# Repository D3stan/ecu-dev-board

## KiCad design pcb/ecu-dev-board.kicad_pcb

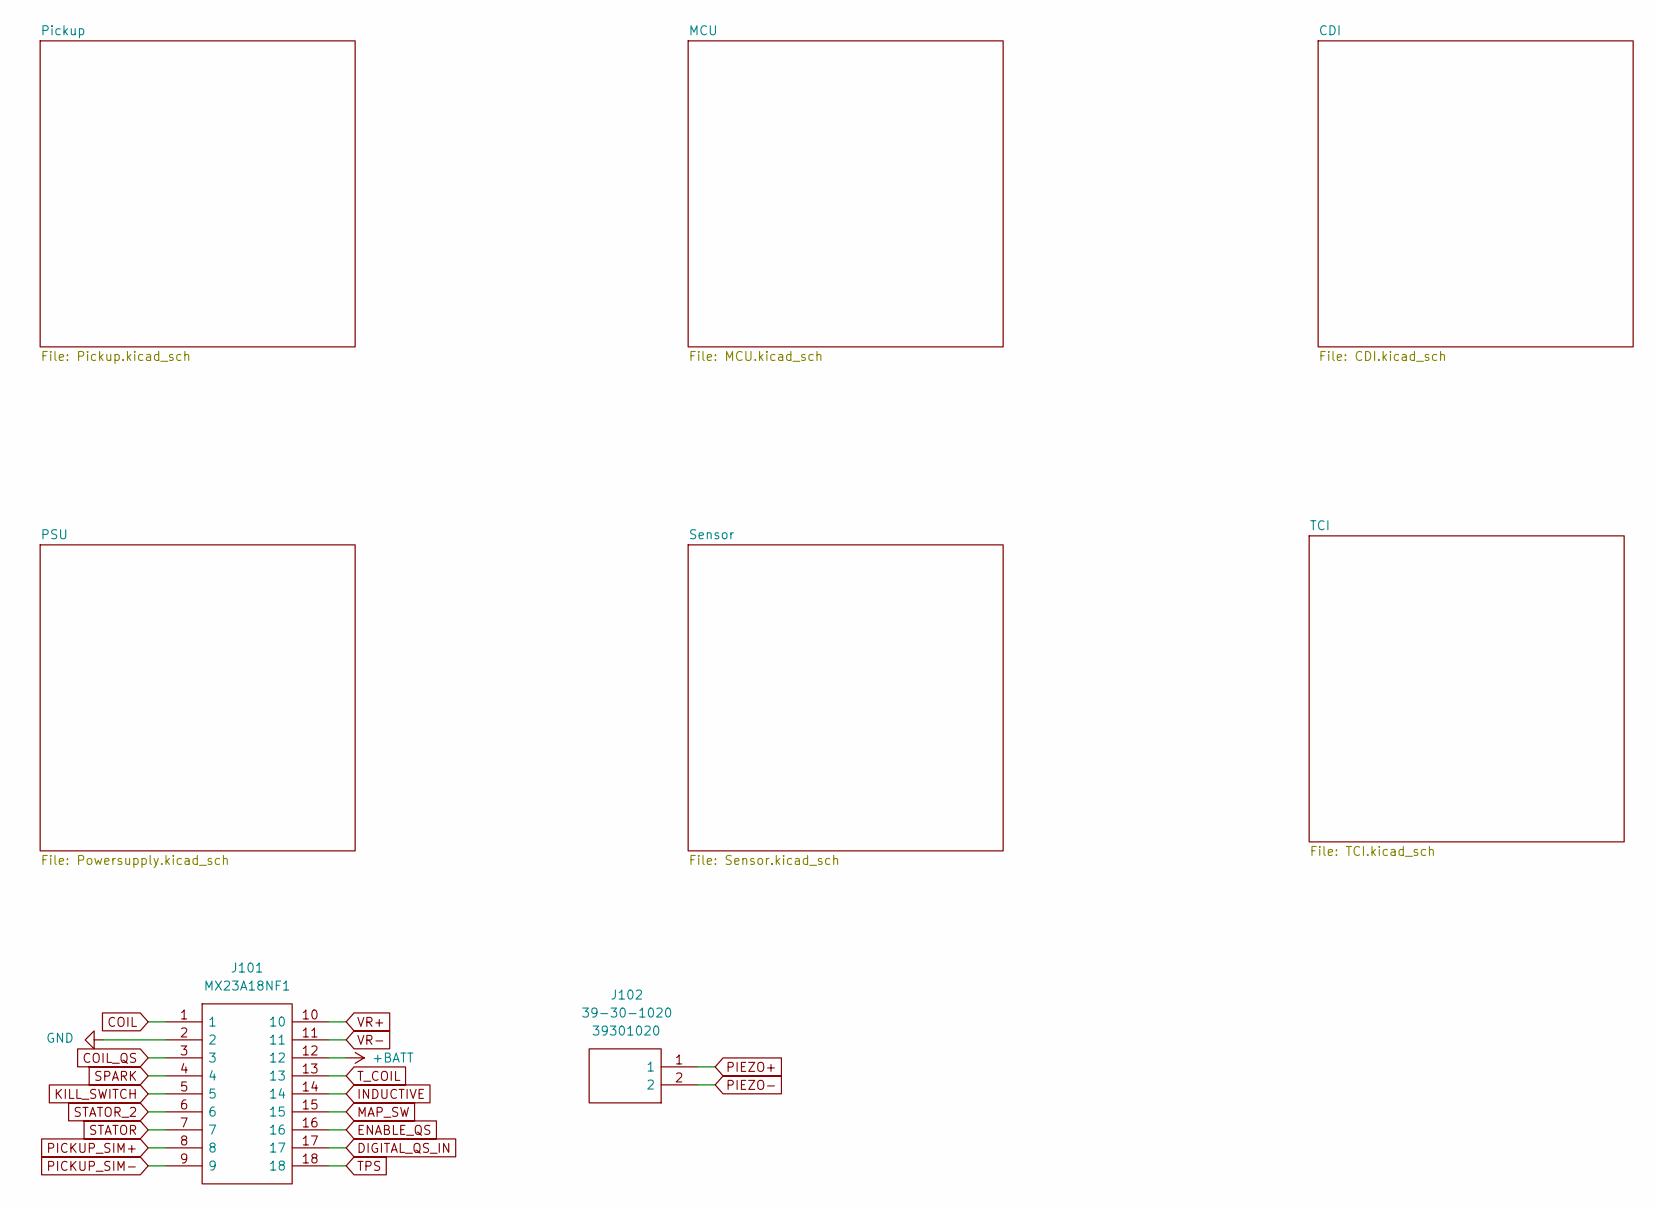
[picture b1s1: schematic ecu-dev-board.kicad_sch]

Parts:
J101: MX23A18NF1; Manufacturer_Part_Number MX23A18NF1; Mouser Part Number 656-MX23A18NF1
J102: 39-30-1020; Molex_Mini-Fit_Jr_5569-02A2_2x01_P4.20mm_Horizontal; Manufacturer_Part_Number 39301020; Mouser Part Number 538-39-30-1020

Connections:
+BATT: J101.12; also elsewhere on the board
COIL: J101.1; also elsewhere on the board
COIL_QS: J101.3; also elsewhere on the board
DIGITAL_QS_IN: J101.17; also elsewhere on the board
ENABLE_QS: J101.16; also elsewhere on the board
INDUCTIVE: J101.14; also elsewhere on the board
KILL_SWITCH: J101.5; also elsewhere on the board
MAP_SW: J101.15; also elsewhere on the board
PICKUP_SIM+: J101.8; also elsewhere on the board
PICKUP_SIM-: J101.9; also elsewhere on the board
PIEZO+: J102.1; also elsewhere on the board
PIEZO-: J102.2; also elsewhere on the board
SPARK: J101.4; also elsewhere on the board
STATOR: J101.7; also elsewhere on the board
STATOR_2: J101.6; also elsewhere on the board
TPS: J101.18; also elsewhere on the board
T_COIL: J101.13; also elsewhere on the board
VR+: J101.10; also elsewhere on the board
VR-: J101.11; also elsewhere on the board

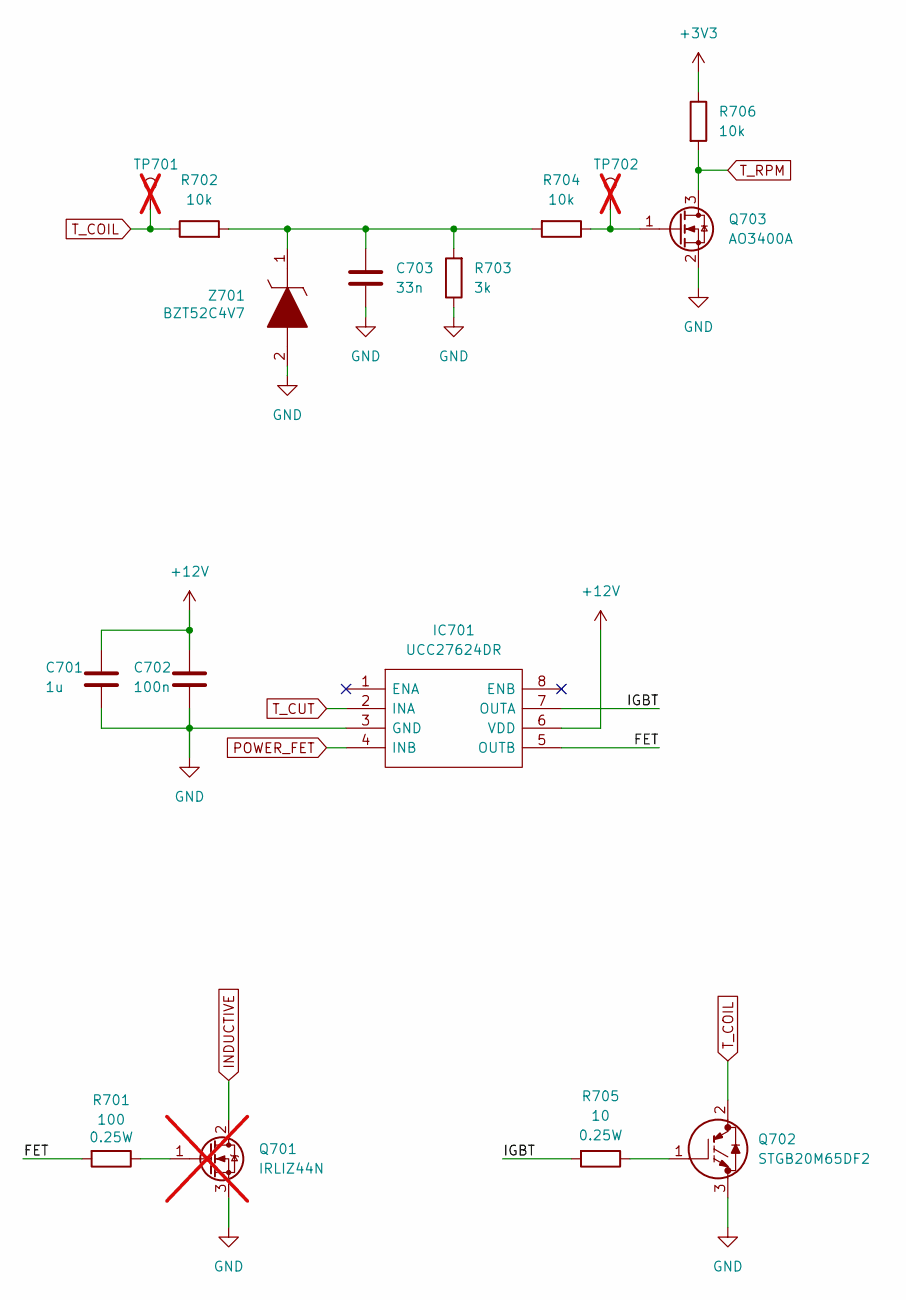
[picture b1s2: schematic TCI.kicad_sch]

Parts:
C701: 1u; C_0805_2012Metric
C702: 100n; C_0805_2012Metric
C703: 33n; C_0805_2012Metric
IC701: UCC27624DR; SOIC127P600X175-8N; Manufacturer_Part_Number UCC27624QDRQ1; Mouser Part Number 595-UCC27624QDRQ1
Q701: IRLIZ44N; TO-220F-3_Vertical; not fitted
Q702: STGB20M65DF2; TO-263-2; Manufacturer_Part_Number STGB20M65DF2; Mouser Part Number 511-STGB20M65DF2
Q703: AO3400A; SOT-23
R701: 100; R_0805_2012Metric
R702, R704, R706: 10k; R_0805_2012Metric
R703: 3k; R_0805_2012Metric
R705: 10; R_0805_2012Metric
TP701, TP702: TestPoint; PinHeader_1x01_P2.54mm_Vertical; not fitted
Z701: BZT52C4V7; D_SOD-123; Manufacturer_Part_Number BZT52B5V1-E3-08; Mouser Part Number 78-BZT52B5V1-E3-08

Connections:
+3V3: R706.1; also elsewhere on the board
+12V: C701.1, C702.1, IC701.6 (VDD); also elsewhere on the board
/TCI/FET: IC701.5 (OUTB), R701.2
/TCI/IGBT: IC701.7 (OUTA), R705.2
INDUCTIVE: Q701.2 (D); also elsewhere on the board
unnamed: C703.1, R702.2, R703.2, R704.2, Z701.1
unnamed: Q701.1 (G), R701.1
unnamed: Q702.1, R705.1
unnamed: Q703.1 (G), R704.1, TP702.1
POWER_FET: IC701.4 (INB); also elsewhere on the board
T_COIL: Q702.2, R702.1, TP701.1; also elsewhere on the board
T_CUT: IC701.2 (INA); also elsewhere on the board
T_RPM: Q703.3 (D), R706.2; also elsewhere on the board

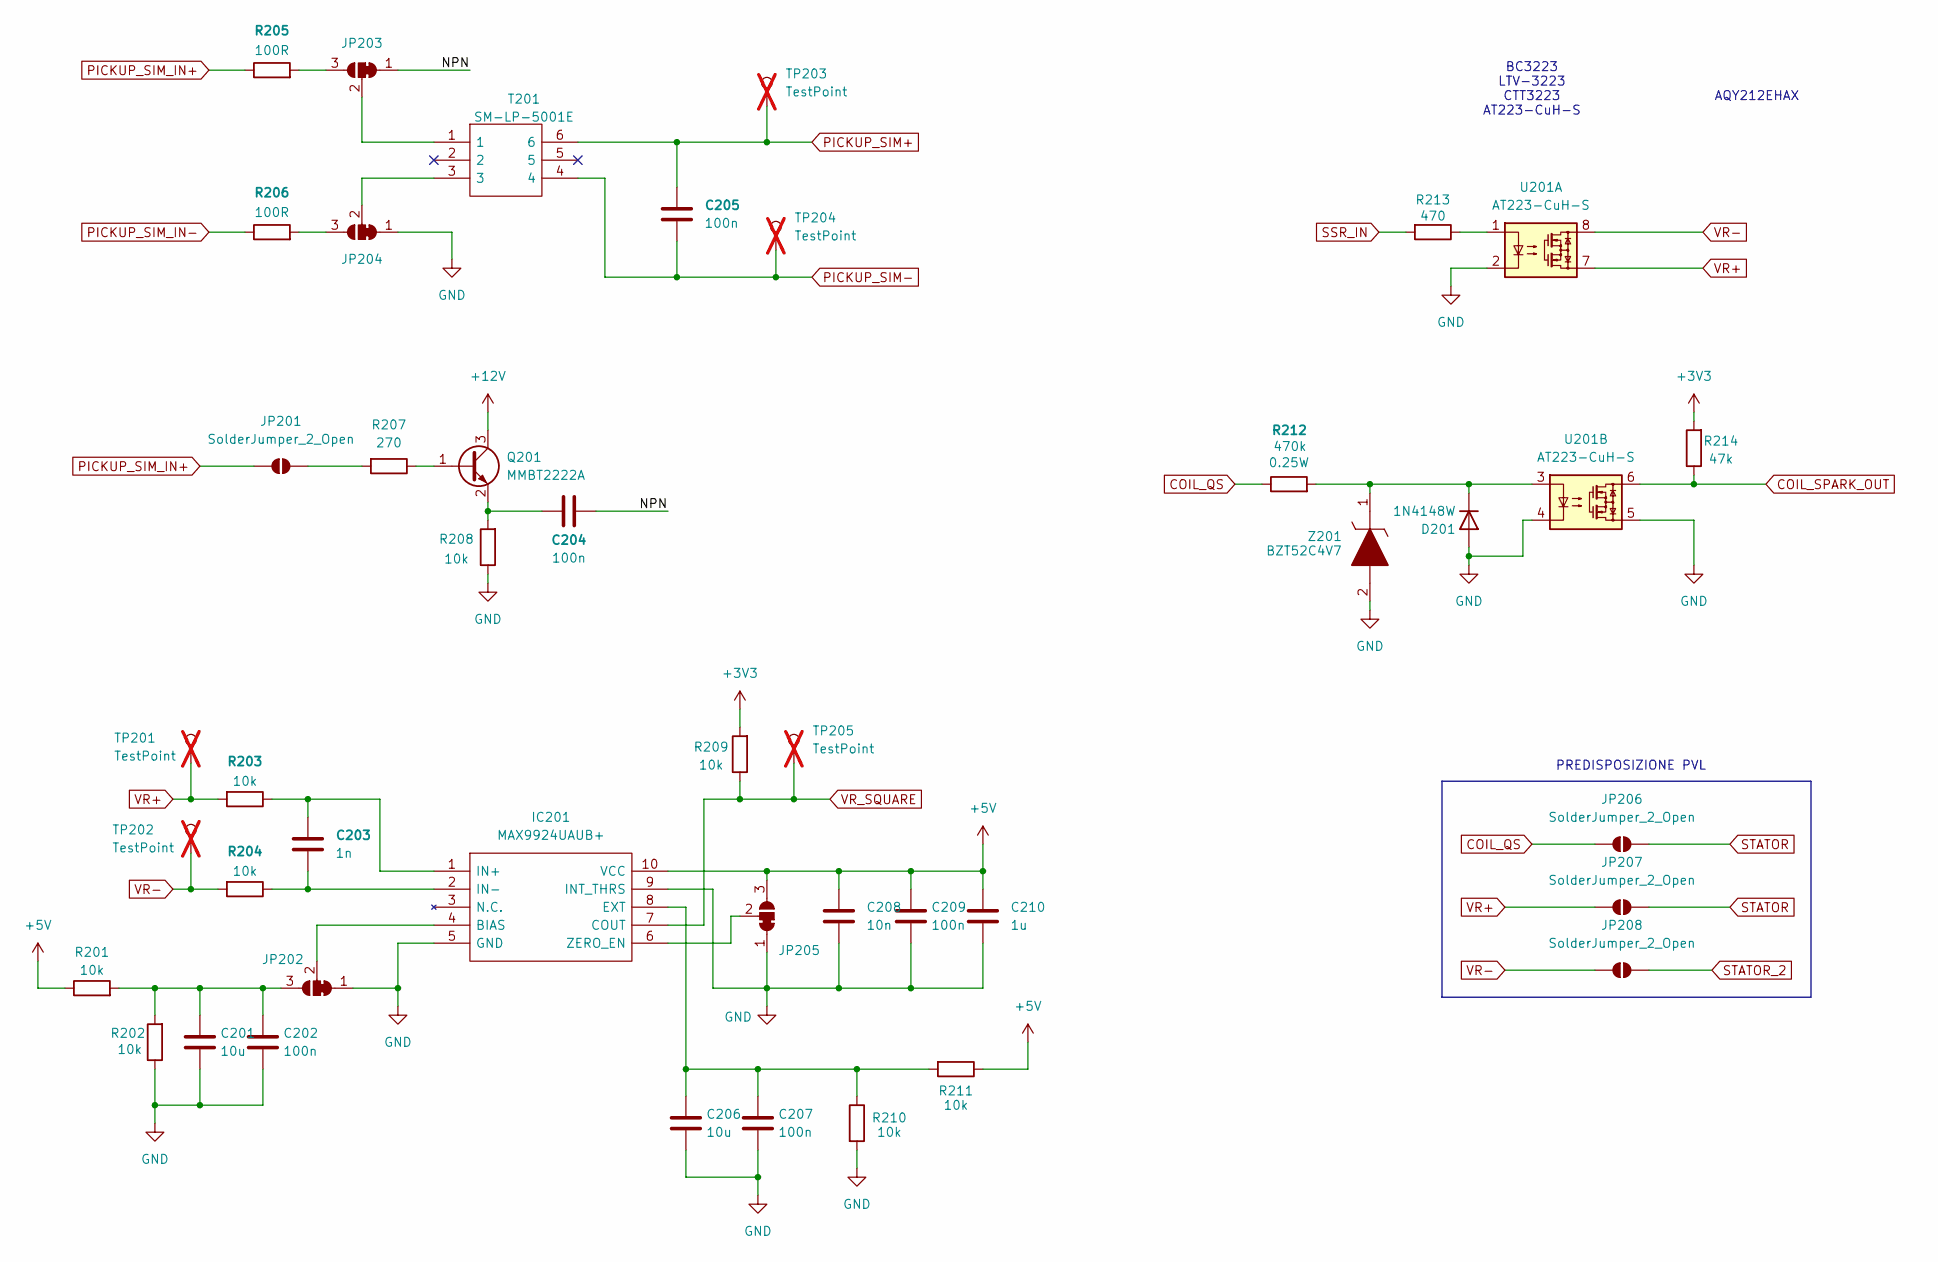
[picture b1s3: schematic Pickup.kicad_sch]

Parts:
C201, C206: 10u; C_0805_2012Metric
C202, C204, C205, C207, C209: 100n; C_0805_2012Metric
C203: 1n; C_0805_2012Metric
C208: 10n; C_0805_2012Metric
C210: 1u; C_0805_2012Metric
D201: 1N4148W; D_SOD-123
IC201: MAX9924UAUB+; SOP50P490X110-10N; Manufacturer_Part_Number MAX9924UAUB+; Mouser Part Number 700-MAX9924UAUB
JP201, JP206, JP207, JP208: SolderJumper_2_Open; SolderJumper-2_P1.3mm_Open_RoundedPad1.0x1.5mm
JP202, JP203, JP204, JP205: SolderJumper_3_Bridged12; SolderJumper-3_P1.3mm_Bridged2Bar12_RoundedPad1.0x1.5mm
Q201: MMBT2222A; SOT-23
R201, R202, R203, R204, R208, R209, R210, R211: 10k; R_0805_2012Metric
R205, R206: 100R; R_0805_2012Metric
R207: 270; R_0603_1608Metric
R212: 470k; R_0805_2012Metric
R213: 470; R_0805_2012Metric
R214: 47k; R_0805_2012Metric
T201: SM-LP-5001E; SMLP5001E; Manufacturer_Part_Number SM-LP-5001E; Mouser Part Number 652-SM-LP-5001E
TP201, TP202, TP203, TP204, TP205: TestPoint; PinHeader_1x01_P2.54mm_Vertical; not fitted
U201: AT223-CuH-S; SOP-8_6.605x9.655mm_P2.54mm
Z201: BZT52C4V7; D_SOD-123; Manufacturer_Part_Number BZT52B5V1-E3-08; Mouser Part Number 78-BZT52B5V1-E3-08

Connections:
+3V3: R209.2, R214.2; also elsewhere on the board
+5V: C208.1, C209.1, C210.1, IC201.10 (VCC), JP205.3 (B), R201.1, R211.1; also elsewhere on the board
+12V: Q201.3 (C); also elsewhere on the board
/Pickup/NPN: C204.1, JP203.1 (A)
COIL_QS: JP206.2 (B), R212.1; also elsewhere on the board
COIL_SPARK_OUT: R214.1, U201.6; also elsewhere on the board
unnamed: D201.1 (K), R212.2, U201.3, Z201.1
unnamed: IC201.4 (BIAS), JP202.2 (C)
unnamed: C206.1, C207.1, IC201.8 (EXT), R210.1, R211.2
unnamed: C203.1, IC201.1 (IN+), R203.1
unnamed: C203.2, IC201.2 (IN-), R204.1
unnamed: IC201.6 (ZERO_EN), JP205.2 (C)
unnamed: JP201.1 (A), R207.2
unnamed: C201.1, C202.1, JP202.3 (B), R201.2, R202.2
unnamed: JP203.3 (B), R205.2
unnamed: JP203.2 (C), T201.1
unnamed: JP204.3 (B), R206.2
unnamed: JP204.2 (C), T201.3
unnamed: Q201.1 (B), R207.1
unnamed: C204.2, Q201.2 (E), R208.2
unnamed: R213.1, U201.1
PICKUP_SIM+: C205.1, T201.6, TP203.1; also elsewhere on the board
PICKUP_SIM-: C205.2, T201.4, TP204.1; also elsewhere on the board
PICKUP_SIM_IN+: JP201.2 (B), R205.1; also elsewhere on the board
PICKUP_SIM_IN-: R206.1; also elsewhere on the board
SSR_IN: R213.2; also elsewhere on the board
STATOR: JP206.1 (A), JP207.1 (A); also elsewhere on the board
STATOR_2: JP208.1 (A); also elsewhere on the board
VR+: JP207.2 (B), R203.2, TP201.1, U201.7; also elsewhere on the board
VR-: JP208.2 (B), R204.2, TP202.1, U201.8; also elsewhere on the board
VR_SQUARE: IC201.7 (COUT), R209.1, TP205.1; also elsewhere on the board

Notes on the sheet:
BC3223 LTV-3223 CTT3223 AT223-CuH-S
PREDISPOSIZIONE PVL
AQY212EHAX

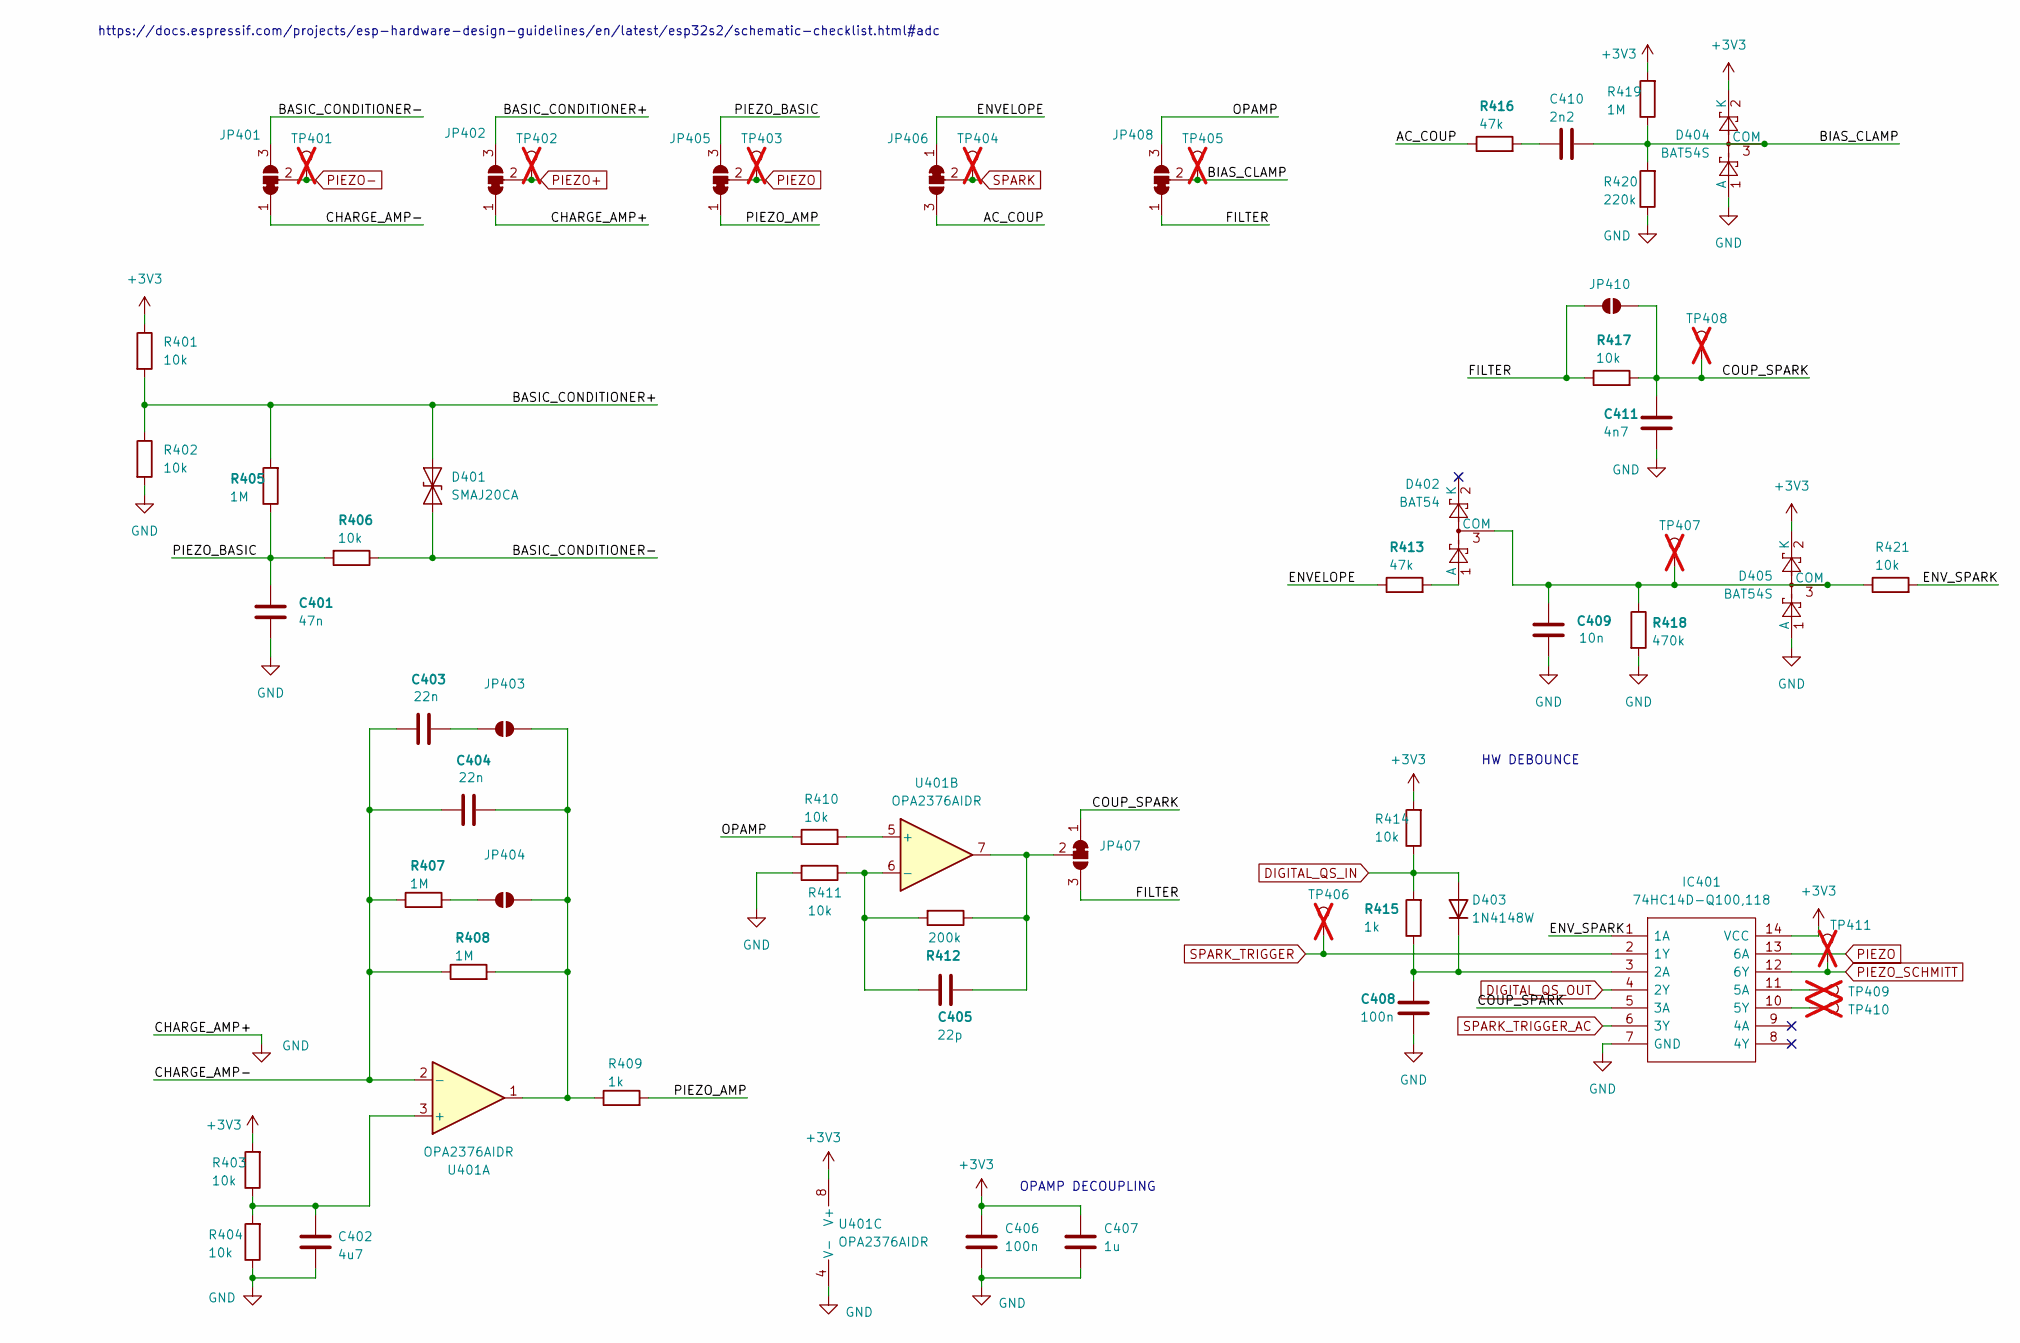
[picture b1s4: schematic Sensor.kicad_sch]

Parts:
C401: 47n; C_0805_2012Metric
C402: 4u7; C_0805_2012Metric
C403, C404: 22n; C_0805_2012Metric
C405: 22p; C_0805_2012Metric
C406, C408: 100n; C_0805_2012Metric
C407: 1u; C_0805_2012Metric
C409: 10n; C_0805_2012Metric
C410: 2n2; C_0805_2012Metric
C411: 4n7; C_0805_2012Metric
D401: SMAJ20CA; D_SMA
D402: BAT54; SOT-23
D403: 1N4148W; D_SOD-123
D404, D405: BAT54S; SOT-23
IC401: 74HC14D-Q100,118; SOIC127P600X175-14N; Manufacturer_Part_Number 74HC14D-Q100,118; Mouser Part Number 771-74HC14D-Q100
JP401, JP402, JP405, JP406, JP407, JP408: SolderJumper_3_Bridged12; SolderJumper-3_P1.3mm_Bridged2Bar12_RoundedPad1.0x1.5mm
JP403, JP404, JP410: SolderJumper_2_Open; SolderJumper-2_P1.3mm_Open_RoundedPad1.0x1.5mm
R401, R402, R403, R404, R406, R410, R411, R414, R417, R421: 10k; R_0805_2012Metric
R405, R407, R408, R419: 1M; R_0805_2012Metric
R409, R415: 1k; R_0805_2012Metric
R412: 200k; R_0805_2012Metric
R413, R416: 47k; R_0805_2012Metric
R418: 470k; R_0805_2012Metric
R420: 220k; R_0805_2012Metric
TP401, TP402, TP403, TP404, TP405, TP406, TP407, TP408, TP409, TP410, TP411: TestPoint; PinHeader_1x01_P2.54mm_Vertical; not fitted
U401: OPA2376AIDR; SOIC127P600X175-8N

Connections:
+3V3: C406.1, C407.1, D404.2 (K), D405.2 (K), IC401.14 (VCC), R401.1, R403.2, R414.2, R419.2, U401.8 (V+); also elsewhere on the board
/Sensor/AC_COUP: JP406.3 (B), R416.1
/Sensor/BASIC_CONDITIONER+: D401.2 (A2), JP402.3 (B), R401.2, R402.1, R405.2
/Sensor/BASIC_CONDITIONER-: D401.1 (A1), JP401.3 (B), R406.1
/Sensor/BIAS_CLAMP: C410.2, D404.3 (COM), JP408.2 (C), R419.1, R420.2, TP405.1
/Sensor/CHARGE_AMP-: C403.1, C404.1, JP401.1 (A), R407.1, R408.1, U401.2 (-)
/Sensor/COUP_SPARK: C411.2, IC401.5 (3A), JP407.1 (A), JP410.1 (A), R417.2, TP408.1
/Sensor/ENVELOPE: JP406.1 (A), R413.1
/Sensor/ENV_SPARK: IC401.1 (1A), R421.2
/Sensor/FILTER: JP407.3 (B), JP408.1 (A), JP410.2 (B), R417.1
/Sensor/OPAMP: JP408.3 (B), R410.1
/Sensor/PIEZO_AMP: JP405.1 (A), R409.2
/Sensor/PIEZO_BASIC: C401.1, JP405.3 (B), R405.1, R406.2
DIGITAL_QS_IN: D403.2 (A), R414.1, R415.2; also elsewhere on the board
DIGITAL_QS_OUT: IC401.4 (2Y); also elsewhere on the board
unnamed: C410.1, R416.2
unnamed: D402.1 (A), R413.2
unnamed: C409.1, D402.3 (COM), D405.3 (COM), R418.1, R421.1, TP407.1
unnamed: C408.2, D403.1 (K), IC401.3 (2A), R415.1
unnamed: IC401.11 (5A), TP409.1
unnamed: IC401.10 (5Y), TP410.1
unnamed: C404.2, JP403.1 (A), JP404.1 (A), R408.2, R409.1, U401.1
unnamed: C403.2, JP403.2 (B)
unnamed: JP404.2 (B), R407.2
unnamed: C405.1, JP407.2 (C), R412.1, U401.7
unnamed: C402.1, R403.1, R404.2, U401.3 (+)
unnamed: R410.2, U401.5 (+)
unnamed: C405.2, R411.1, R412.2, U401.6 (-)
PIEZO: IC401.13 (6A), JP405.2 (C), TP403.1; also elsewhere on the board
PIEZO+: JP402.2 (C), TP402.1; also elsewhere on the board
PIEZO-: JP401.2 (C), TP401.1; also elsewhere on the board
PIEZO_SCHMITT: IC401.12 (6Y), TP411.1; also elsewhere on the board
SPARK: JP406.2 (C), TP404.1; also elsewhere on the board
SPARK_TRIGGER: IC401.2 (1Y), TP406.1; also elsewhere on the board
SPARK_TRIGGER_AC: IC401.6 (3Y); also elsewhere on the board

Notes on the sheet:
HW DEBOUNCE
OPAMP DECOUPLING
https://docs.espressif.com/projects/esp-hardware-design-guidelines/en/latest/esp32s2/schematic-checklist.html#adc

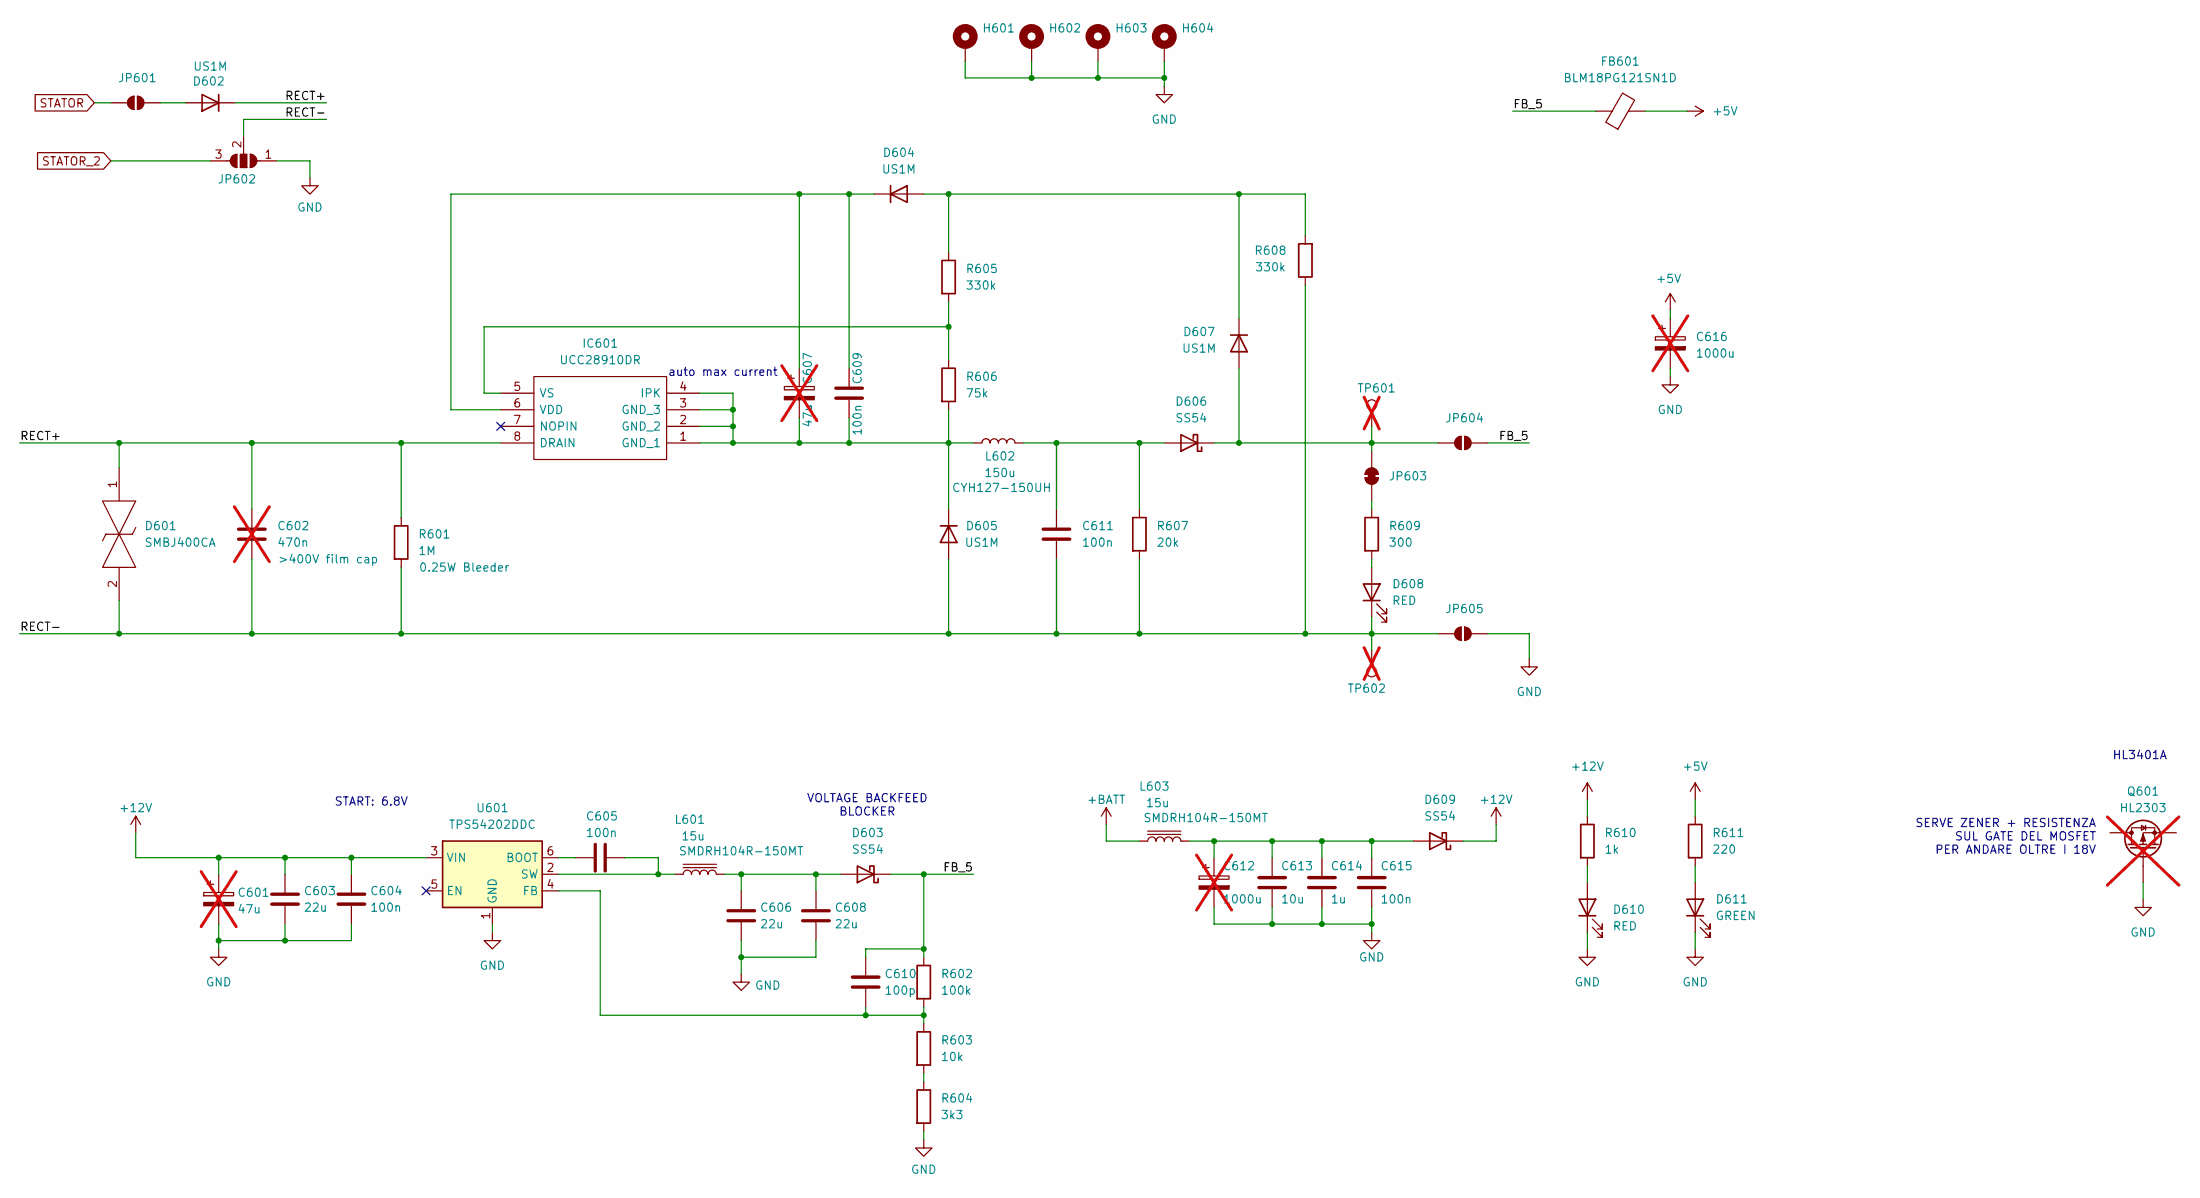
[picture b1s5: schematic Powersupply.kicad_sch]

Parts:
C601, C607: 47u; CP_Radial_D5.0mm_P2.50mm; not fitted
C602: 470n; C_Rect_L7.0mm_W2.0mm_P5.00mm; not fitted
C603, C606, C608: 22u; C_0805_2012Metric
C604, C605, C609, C611, C615: 100n; C_0805_2012Metric
C610: 100p; C_0603_1608Metric
C612, C616: 1000u; CP_Radial_D8.0mm_P5.00mm; not fitted
C613: 10u; C_0805_2012Metric
C614: 1u; C_0805_2012Metric
D601: SMBJ400CA; DIONM5436X261N; Manufacturer_Part_Number SMBJ400CA; Mouser Part Number 576-SMBJ400CA
D602, D604, D605, D607: US1M; D_SMA
D603, D606, D609: SS54; D_SMA
D608, D610: RED; LED_0805_2012Metric
D611: GREEN; LED_0805_2012Metric
FB601: BLM18PG121SN1D; L_0603_1608Metric
H601, H602, H603, H604: MountingHole_Pad; MountingHole_3.2mm_M3_DIN965_Pad
IC601: UCC28910DR; SOIC127P600X175-8N; Manufacturer_Part_Number UCC28910DR; Mouser Part Number 595-UCC28910DR
JP601, JP604, JP605: SolderJumper_2_Open; SolderJumper-2_P1.3mm_Open_RoundedPad1.0x1.5mm
JP602: SolderJumper_3_Open; SolderJumper-3_P1.3mm_Open_RoundedPad1.0x1.5mm
JP603: SolderJumper_2_Bridged; SolderJumper-2_P1.3mm_Bridged_RoundedPad1.0x1.5mm
L601, L603: 15u; L_10.4x10.4_H4.8
L602: 150u; L_SXN_SMDRI127
Q601: HL2303; SOT-23; not fitted
R601: 1M; R_0805_2012Metric
R602: 100k; R_0805_2012Metric
R603: 10k; R_0805_2012Metric
R604: 3k3; R_0805_2012Metric
R605, R608: 330k; R_0603_1608Metric
R606: 75k; R_0603_1608Metric
R607: 20k; R_0805_2012Metric
R609: 300; R_0805_2012Metric
R610: 1k; R_0805_2012Metric
R611: 220; R_0805_2012Metric
TP601, TP602: TestPoint; PinHeader_1x01_P2.54mm_Vertical; not fitted
U601: TPS54202DDC; SOT-23-6

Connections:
+5V: C616.1, FB601.2, R611.1; also elsewhere on the board
+12V: C601.1, C603.1, C604.1, D609.1 (K), R610.1, U601.3 (VIN); also elsewhere on the board
+BATT: L603.1; also elsewhere on the board
/PSU/FB_5: C610.1, D603.1 (K), FB601.1, JP604.2 (B), R602.1
/PSU/RECT+: C602.1, D601.1, D602.1 (K), IC601.8 (DRAIN), R601.1
/PSU/RECT-: C602.2, C611.2, D601.2, D605.2 (A), D608.1 (K), JP602.2 (C), JP605.1 (A), R601.2, R607.2, R608.1, TP602.1
unnamed: D602.2 (A), JP601.2 (B)
unnamed: C606.1, C608.1, D603.2 (A), L601.2
unnamed: D604.2 (A), D607.1 (K), R605.1, R608.2
unnamed: C607.1, C609.1, D604.1 (K), IC601.6 (VDD)
unnamed: C607.2, C609.2, D605.1 (K), IC601.1 (GND_1), IC601.2 (GND_2), IC601.3 (GND_3), IC601.4 (IPK), L602.1, R606.2
unnamed: C611.1, D606.2 (A), L602.2, R607.1
unnamed: D606.1 (K), D607.2 (A), JP603.2 (B), JP604.1 (A), TP601.1
unnamed: D608.2 (A), R609.2
unnamed: C612.1, C613.1, C614.1, C615.1, D609.2 (A), L603.2
unnamed: D610.2 (A), R610.2
unnamed: D611.2 (A), R611.2
unnamed: IC601.5 (VS), R605.2, R606.1
unnamed: JP603.1 (A), R609.1
unnamed: R603.2, R604.1
unnamed: C605.1, U601.6 (BOOT)
unnamed: C610.2, R602.2, R603.1, U601.4 (FB)
unnamed: C605.2, L601.1, U601.2 (SW)
STATOR: JP601.1 (A); also elsewhere on the board
STATOR_2: JP602.3 (B); also elsewhere on the board

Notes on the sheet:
START: 6.8V
auto max current
HL3401A
VOLTAGE BACKFEED BLOCKER
SERVE ZENER + RESISTENZA SUL GATE DEL MOSFET PER ANDARE OLTRE I 18V

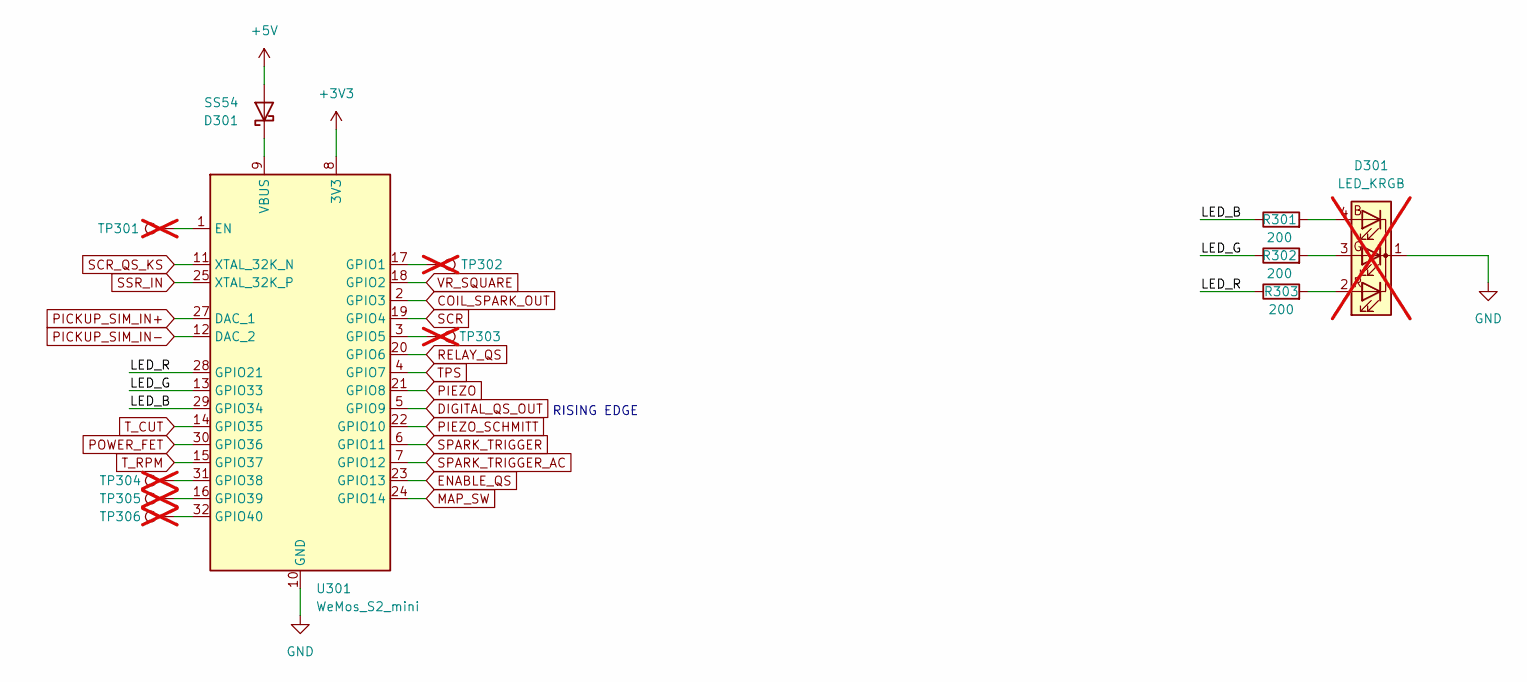
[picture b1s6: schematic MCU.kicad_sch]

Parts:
D301: LED_KRGB; LED_D5.0mm-4_RGB_Wide_Pins; not fitted
R301, R302, R303: 200; R_0805_2012Metric
TP301, TP302, TP303, TP304, TP305, TP306: TestPoint; PinHeader_1x01_P2.54mm_Vertical; not fitted
U301: WeMos_S2_mini; WEMOS_S2_mini

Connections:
+3V3: U301.8 (3V3); also elsewhere on the board
/MCU/LED_B: R301.1, U301.29 (GPIO34)
/MCU/LED_G: R302.1, U301.13 (GPIO33)
/MCU/LED_R: R303.1, U301.28 (GPIO21)
COIL_SPARK_OUT: U301.2 (GPIO3); also elsewhere on the board
DIGITAL_QS_OUT: U301.5 (GPIO9); also elsewhere on the board
ENABLE_QS: U301.23 (GPIO13); also elsewhere on the board
MAP_SW: U301.24 (GPIO14); also elsewhere on the board
unnamed: D301.4 (BA), R301.2
unnamed: D301.3 (GA), R302.2
unnamed: D301.2 (RA), R303.2
unnamed: TP301.1, U301.1 (EN)
unnamed: TP302.1, U301.17 (GPIO1)
unnamed: TP303.1, U301.3 (GPIO5)
unnamed: TP304.1, U301.31 (GPIO38)
unnamed: TP305.1, U301.16 (GPIO39)
unnamed: TP306.1, U301.32 (GPIO40)
PICKUP_SIM_IN+: U301.27 (DAC_1); also elsewhere on the board
PICKUP_SIM_IN-: U301.12 (DAC_2); also elsewhere on the board
PIEZO: U301.21 (GPIO8); also elsewhere on the board
PIEZO_SCHMITT: U301.22 (GPIO10); also elsewhere on the board
POWER_FET: U301.30 (GPIO36); also elsewhere on the board
RELAY_QS: U301.20 (GPIO6); also elsewhere on the board
SCR: U301.19 (GPIO4); also elsewhere on the board
SCR_QS_KS: U301.11 (XTAL_32K_N); also elsewhere on the board
SPARK_TRIGGER: U301.6 (GPIO11); also elsewhere on the board
SPARK_TRIGGER_AC: U301.7 (GPIO12); also elsewhere on the board
SSR_IN: U301.25 (XTAL_32K_P); also elsewhere on the board
TPS: U301.4 (GPIO7); also elsewhere on the board
T_CUT: U301.14 (GPIO35); also elsewhere on the board
T_RPM: U301.15 (GPIO37); also elsewhere on the board
VR_SQUARE: U301.18 (GPIO2); also elsewhere on the board

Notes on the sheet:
RISING EDGE

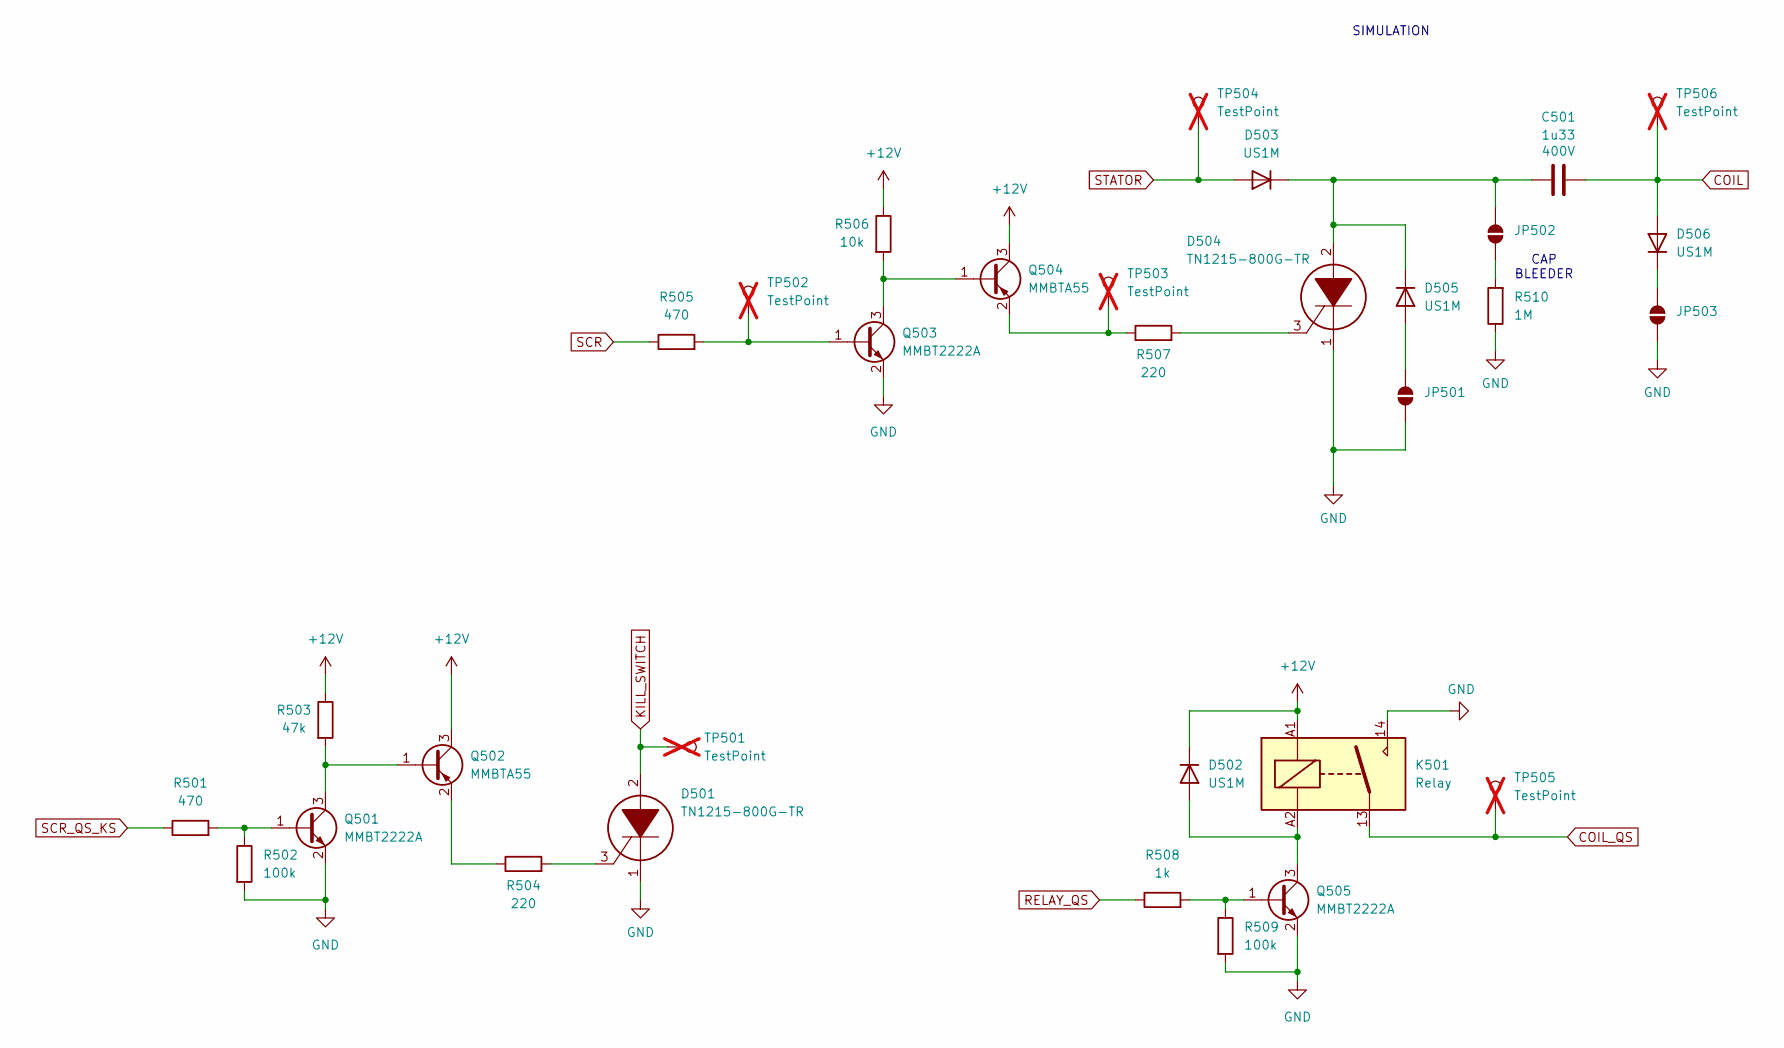
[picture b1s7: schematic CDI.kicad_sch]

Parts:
C501: 1u33; C_Axial_L17.0mm_D6.5mm_P20.00mm_Horizontal
D501, D504: TN1215-800G-TR; TO-263-2; Manufacturer_Part_Number TN1215-800G-TR; Mouser Part Number 511-TN1215-800G-TR
D502, D503, D505, D506: US1M; D_SMA
JP501, JP502, JP503: SolderJumper_2_Open; SolderJumper-2_P1.3mm_Open_RoundedPad1.0x1.5mm
K501: Relay; Ext_Relay
Q501, Q503, Q505: MMBT2222A; SOT-23
Q502, Q504: MMBTA55; SOT-23
R501, R505: 470; R_0805_2012Metric
R502, R509: 100k; R_0805_2012Metric
R503: 47k; R_0805_2012Metric
R504, R507: 220; R_0805_2012Metric
R506: 10k; R_0805_2012Metric
R508: 1k; R_0805_2012Metric
R510: 1M; R_0805_2012Metric
TP501, TP502, TP503, TP504, TP505, TP506: TestPoint; PinHeader_1x01_P2.54mm_Vertical; not fitted

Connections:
+12V: D502.1 (K), K501.A1, Q502.3 (C), Q504.3 (C), R503.1, R506.1; also elsewhere on the board
COIL: C501.2, D506.2 (A), TP506.1; also elsewhere on the board
COIL_QS: K501.13, TP505.1; also elsewhere on the board
KILL_SWITCH: D501.2, TP501.1; also elsewhere on the board
unnamed: D501.3, R504.2
unnamed: D502.2 (A), K501.A2, Q505.3 (C)
unnamed: C501.1, D503.1 (K), D504.2, D505.1 (K), JP502.2 (B)
unnamed: D504.3, R507.2
unnamed: D505.2 (A), JP501.2 (B)
unnamed: D506.1 (K), JP503.2 (B)
unnamed: JP502.1 (A), R510.2
unnamed: Q501.1 (B), R501.2, R502.1
unnamed: Q501.3 (C), Q502.1 (B), R503.2
unnamed: Q502.2 (E), R504.1
unnamed: Q503.1 (B), R505.2, TP502.1
unnamed: Q503.3 (C), Q504.1 (B), R506.2
unnamed: Q504.2 (E), R507.1, TP503.1
unnamed: Q505.1 (B), R508.2, R509.1
RELAY_QS: R508.1; also elsewhere on the board
SCR: R505.1; also elsewhere on the board
SCR_QS_KS: R501.1; also elsewhere on the board
STATOR: D503.2 (A), TP504.1; also elsewhere on the board

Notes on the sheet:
SIMULATION
CAP BLEEDER

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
